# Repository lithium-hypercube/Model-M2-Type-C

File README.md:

# Model M2 Type C
This project is a new board for the IBM model M2 that supports USB C

## Features
- USB C
- Has QMK and its features (allows key remapping)
- Less power draw (probably)
- Open source

## Usage
1. Print the board either using a cheap foreign service such as [JLCPBC](https://jlcpcb.com/ "JLCPBC") for around $2-6 + shipping, or a domestic service such as [OSH Park](https://oshpark.com/ "OSH Park") for around $22.
2. Acquire the components

|Reference|Type     |Value         |Qty|Link                           |
|---------|---------|--------------|---|-------------------------------|
|C1,C2    |Capacitor|22pF          |2  |                               |
|C3       |Capacitor|1uF           |1  |                               |
|C4,C5,C6 |Capacitor|0.1uF         |3  |                               |
|C7       |Capacitor|10uF          |1  |                               |
|D1,D2,D3 |LED      |Green, 3.3v   |3  |                               |
|F1       |Fuse     |500mA         |1  |https://mou.sr/447NG73         |
|R1,R2    |Resistor |5.1k          |2  |                               |
|R3,R4    |Resistor |22            |2  |                               |
|R5,R6    |Resistor |10k           |2  |                               |
|R7,R8,R9 |Resistor |270           |3  |                               |
|SW1      |Button   |6xH7.3mm      |1  |https://mou.sr/4krX0sq         |
|U1       |ESD Diode|PRTR5V0U2X    |1  |https://mou.sr/3vXlnaQ         |
|U2       |Chip     |AT90USB1286-AU|1  |https://mou.sr/4kNduMC         |
|Y1       |Crystal  |16MHz         |1  |https://mou.sr/4ebH8ZG         |
|USB1     |Port     |TYPE-C-31-M-12|1  |[keeb.io link](https://keeb.io/products/usb-c-port-12-pin-hro-type-c-31-m-12 "USB-C Port - 12-pin - HRO")|
|         |Screw    |M3            |1  |Harvest from the old board ([or buy an alternative](https://www.mcmaster.com/91223A411/ "McMASTER-CARR part 91223A411"))|
3. Put it together. It's possible to solder the SMD components manually with a soldering iron, but if you are able to find a hot air gun or a reflow oven, it'll be easier. Reference the visual BOM to see what goes where (it is located in [bom/ibom.html](https://htmlpreview.github.io/?https://github.com/lithium-hypercube/Model-M2-Type-C/blob/master/bom/ibom.html "Interactive bill of materials link")).
	- You should have balls of solder instead of pointy solder joints on the underside of the PCB to not damage the membrane. To do this:
		1. Solder the components to the board normally
		2. Use side cutters to cut away the solder/remaining component legs on the underside (except the screw). Try to cut close to the PCB but don't damage the traces.
		3. Add more solder/flux to the pad. Try to get a smooth blob of solder. Don't add too much though
5. Install firmware and test the board by shorting some pads (carefully)
6. Cut the keyboard's case to make the USB C connector hole larger (I used a fretsaw to do this)

The traces on the membrane may have corroded over time. You can use a multimeter to check for connectivity. Note that trace resistance might be high, so the multimeter might not make a sound even if there is a connection. Try not to scratch the traces. I used conductive copper tape (one where the sticky side is also conductive) to repair damaged traces on mine.

The exposed traces on the membrane that touch the board did not provide a stable connection in my case. Try using a conductive pen (like a circuitscribe) to repaint them (I tried using copper tape but the connection was unreliable). Pushing down on the board might sometimes temporarily resolve the problem.

## Firmware
This board is fully compatible with QMK.

To install the firmware to your keyboard:
- Clone the qmk_firmware repo
	```
	git clone https://github.com/lithium-hypercube/qmk_firmware
	```
- [Setup the build environment](https://docs.qmk.fm/#/getting_started_build_tools)
- [Enter the keyboard into bootloader mode](https://github.com/lithium-hypercube/qmk_firmware/tree/master/keyboards/ibm/model_m2/m2_usbc#bootloader "Link to QMK firmware readme")
- Make and flash the firmware
	```
	make ibm/model_m2/m2_usbc:default:flash
	```
[More details](https://github.com/lithium-hypercube/qmk_firmware/tree/master/keyboards/ibm/model_m2/m2_usbc "Link to QMK firmware")

Note that the firmware only supports the ANSI layout, but you can probably fix that pretty easily if you have access to the ISO one (I don't). Most keys should work even if you use the wrong one.

## Other
If you have any problems/comments, or find anything that could be improved, please submit issue or a pull request!

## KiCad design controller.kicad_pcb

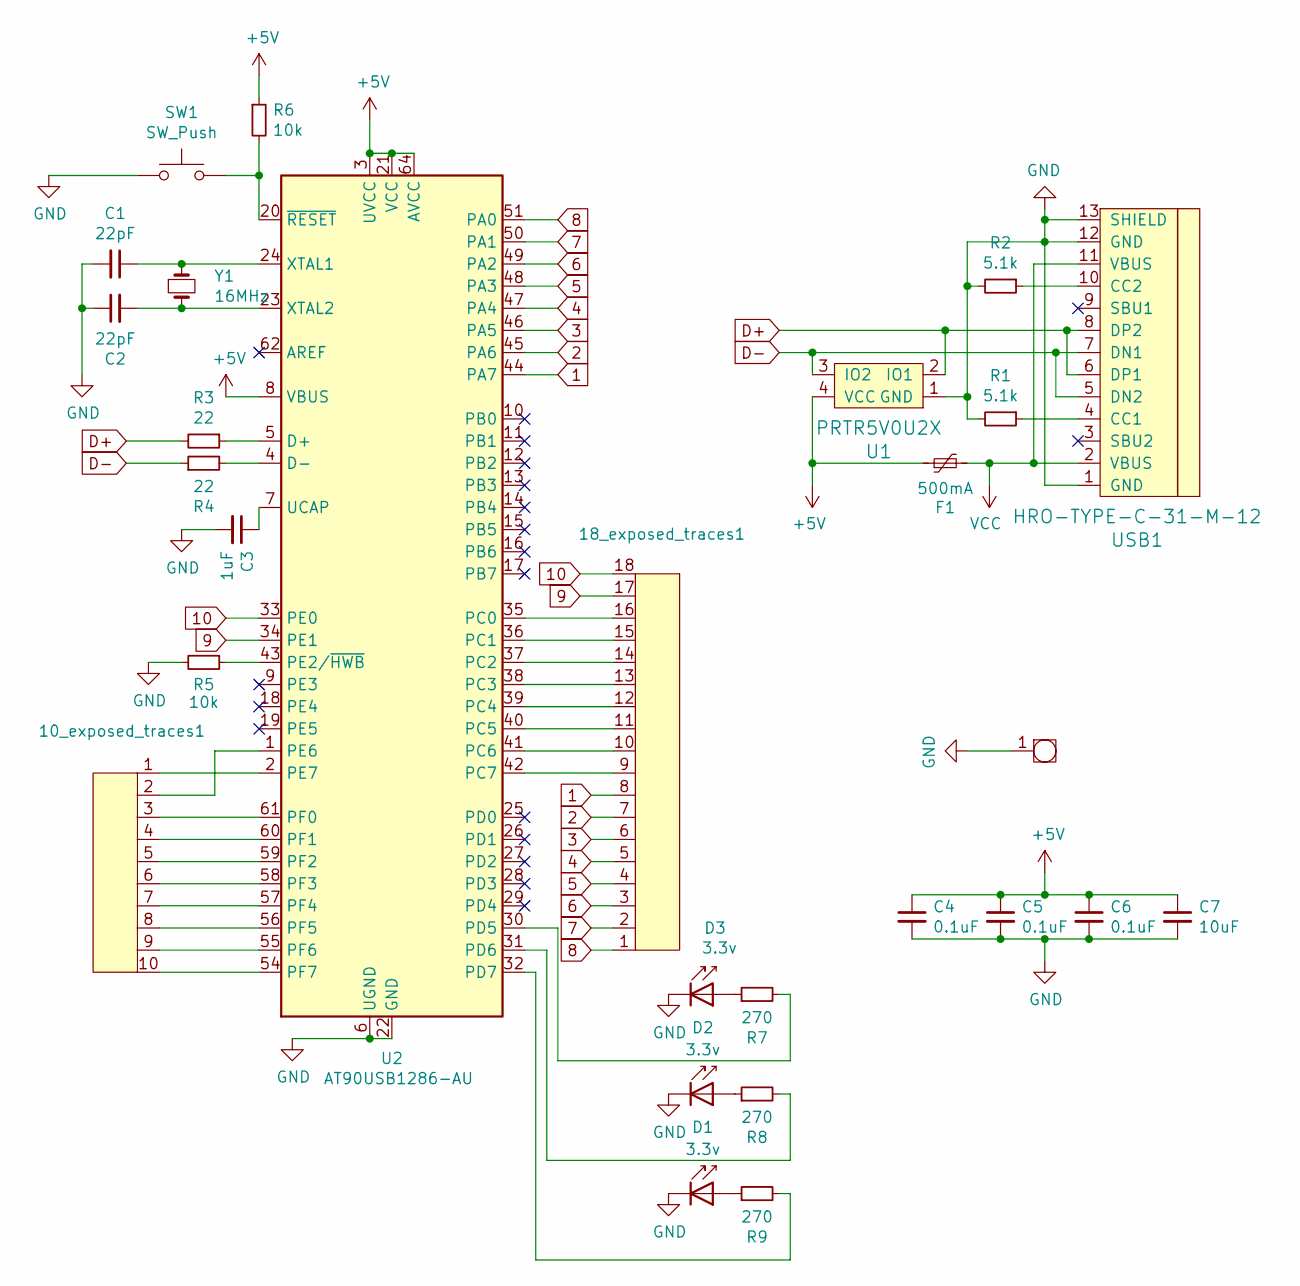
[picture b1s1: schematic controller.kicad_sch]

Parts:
10_exposed_traces1: 10_exposed_traces
18_exposed_traces1: 18_exposed_traces
C1, C2: 22pF; C_Disc_D5.0mm_W2.5mm_P5.00mm
C3: 1uF; C_Disc_D5.0mm_W2.5mm_P5.00mm
C4, C5, C6: 0.1uF; C_Disc_D5.0mm_W2.5mm_P5.00mm
C7: 10uF; C_Disc_D5.0mm_W2.5mm_P5.00mm
D1, D2, D3: 3.3v; LED_D5.0mm_IRGrey
F1: 500mA; Littlefuse 0251.500MRT1L
R1, R2: 5.1k; R_Axial_DIN0207_L6.3mm_D2.5mm_P10.16mm_Horizontal
R3, R4: 22; R_Axial_DIN0207_L6.3mm_D2.5mm_P10.16mm_Horizontal
R5, R6: 10k; R_Axial_DIN0207_L6.3mm_D2.5mm_P10.16mm_Horizontal
R7, R8, R9: 270; R_Axial_DIN0207_L6.3mm_D2.5mm_P10.16mm_Horizontal
SW1: SW_Push; SW_PUSH_6mm_H7.3mm
U1: PRTR5V0U2X; SOT143B_silkscreen_compatibility
U2: AT90USB1286-AU; TQFP-64_14x14mm_P0.8mm
U3: screw
USB1: HRO-TYPE-C-31-M-12; HRO-TYPE-C-31-M-12-HandSoldering
Y1: 16MHz; Crystal_HC49-U_Vertical

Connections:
1: 18_exposed_traces1.8, U2.44 (PA7)
2: 18_exposed_traces1.7, U2.45 (PA6)
3: 18_exposed_traces1.6, U2.46 (PA5)
4: 18_exposed_traces1.5, U2.47 (PA4)
5: 18_exposed_traces1.4, U2.48 (PA3)
6: 18_exposed_traces1.3, U2.49 (PA2)
7: 18_exposed_traces1.2, U2.50 (PA1)
8: 18_exposed_traces1.1, U2.51 (PA0)
9: 18_exposed_traces1.17, U2.34 (PE1)
10: 18_exposed_traces1.18, U2.33 (PE0)
+5V: C4.1, C5.1, C6.1, C7.1, F1.1, R6.1, U1.4 (VCC), U2.3 (UVCC), U2.8 (VBUS), U2.21 (VCC), U2.52 (VCC), U2.64 (AVCC)
D+: R3.2, U1.2 (IO1), USB1.6 (DP1), USB1.8 (DP2)
D-: R4.1, U1.3 (IO2), USB1.5 (DN2), USB1.7 (DN1)
GND: C1.2, C2.1, C3.2, C4.2, C5.2, C6.2, C7.2, D1.1 (K), D2.1 (K), D3.1 (K), R1.2, R2.2, R5.2, SW1.1, U1.1 (GND), U2.6 (UGND), U2.22 (GND), U2.53 (GND), U2.63 (GND), U3.1, USB1.1 (GND), USB1.12 (GND), USB1.13 (SHIELD)
unnamed: D1.2 (A), R9.1
unnamed: D2.2 (A), R8.1
unnamed: D3.2 (A), R7.1
unnamed: R3.1, U2.5 (D+)
unnamed: R4.2, U2.4 (D-)
unnamed: 18_exposed_traces1.16, U2.35 (PC0)
unnamed: 18_exposed_traces1.15, U2.36 (PC1)
unnamed: 18_exposed_traces1.14, U2.37 (PC2)
unnamed: 18_exposed_traces1.13, U2.38 (PC3)
unnamed: 18_exposed_traces1.12, U2.39 (PC4)
unnamed: 18_exposed_traces1.11, U2.40 (PC5)
unnamed: 18_exposed_traces1.10, U2.41 (PC6)
unnamed: 18_exposed_traces1.9, U2.42 (PC7)
unnamed: R7.2, U2.30 (PD5)
unnamed: R8.2, U2.31 (PD6)
unnamed: R9.2, U2.32 (PD7)
unnamed: R5.1, U2.43 (PE2/~HWB)
unnamed: 10_exposed_traces1.2, U2.1 (PE6)
unnamed: 10_exposed_traces1.1, U2.2 (PE7)
unnamed: 10_exposed_traces1.3, U2.61 (PF0)
unnamed: 10_exposed_traces1.4, U2.60 (PF1)
unnamed: 10_exposed_traces1.5, U2.59 (PF2)
unnamed: 10_exposed_traces1.6, U2.58 (PF3)
unnamed: 10_exposed_traces1.7, U2.57 (PF4)
unnamed: 10_exposed_traces1.8, U2.56 (PF5)
unnamed: 10_exposed_traces1.9, U2.55 (PF6)
unnamed: 10_exposed_traces1.10, U2.54 (PF7)
unnamed: C3.1, U2.7 (UCAP)
unnamed: C1.1, U2.24 (XTAL1), Y1.1
unnamed: C2.2, U2.23 (XTAL2), Y1.2
unnamed: R6.2, SW1.2, U2.20 (~RESET)
unnamed: R1.1, USB1.4 (CC1)
unnamed: R2.1, USB1.10 (CC2)
VCC: F1.2, USB1.2 (VBUS), USB1.11 (VBUS)

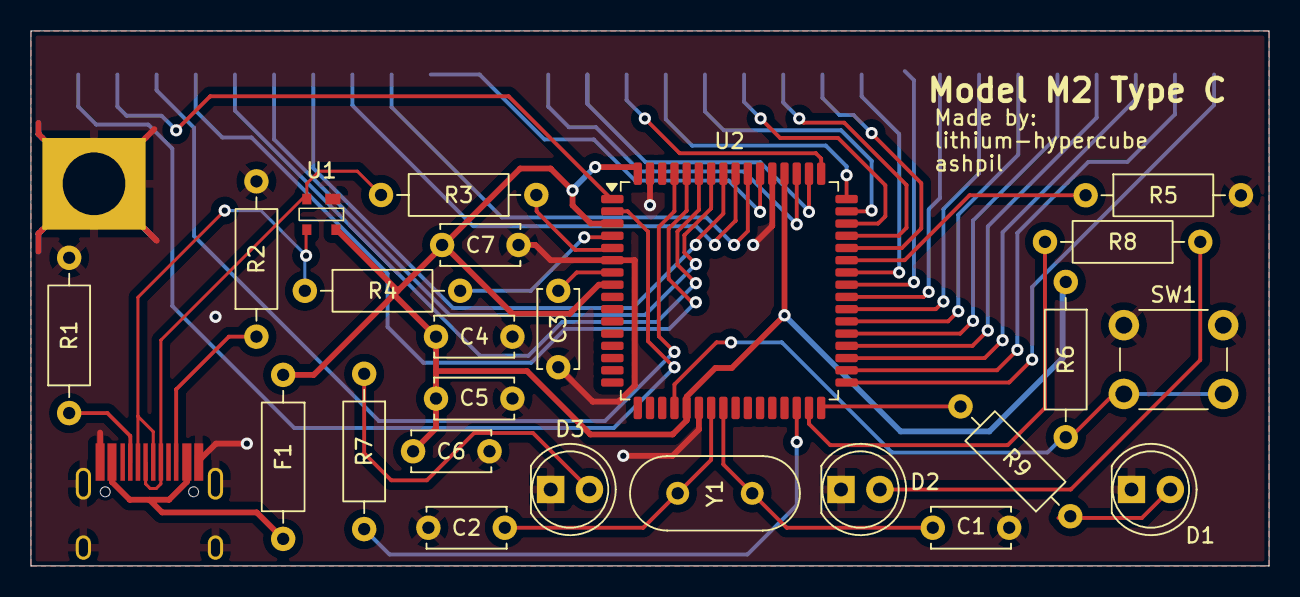
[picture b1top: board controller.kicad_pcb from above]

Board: 2 copper layers, 81.0 x 35.0 mm, 28 parts (0 on the bottom side), 48 nets.

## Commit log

2025-06-17 Make it compatible with the M2
2025-06-20 Fix table (probably)
2025-06-20 Fix table (probably) (again)
2025-06-20 Remove reference to nonexistent file
2025-06-20 Reorganize images
2025-06-20 Remove important information section
2025-06-20 Make soldering section more readable
2025-06-20 Improve soldering instructions
2025-06-20 Make usage instructions clearer
2025-06-20 Fix firmware section formatting
2025-06-24 Fix capitalization mistake
2025-06-24 Add tactile switch size
2025-06-24 Add firmware instructions and link
2025-06-24 Improve firmware section formatting
2025-06-25 Add more firmware instructions
2025-06-25 Fix firmware markdown
2025-06-25 Remove backups and add build environment link
2025-06-25 Actually remove backups this time
2025-06-25 Add ibom link
2025-07-01 Add images
2025-07-04 Change model m to model m2
2025-07-06 Update components list and edit traces section
2025-07-06 Add button link
2025-07-06 Add a trace
2025-07-06 Update render
2025-07-08 Clarify solder joint instruction
